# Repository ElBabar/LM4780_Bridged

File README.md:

# LM4780_Bridged

LM4780 (gainclone) amplifier board, bridged design (mono).

Bridged design of the LM4780, provides 120W, one channel.

Supply +40, -40, GND

You might need to use my library:
add https://github.com/ElBabar/Libabar.git
to your KiCad paths.

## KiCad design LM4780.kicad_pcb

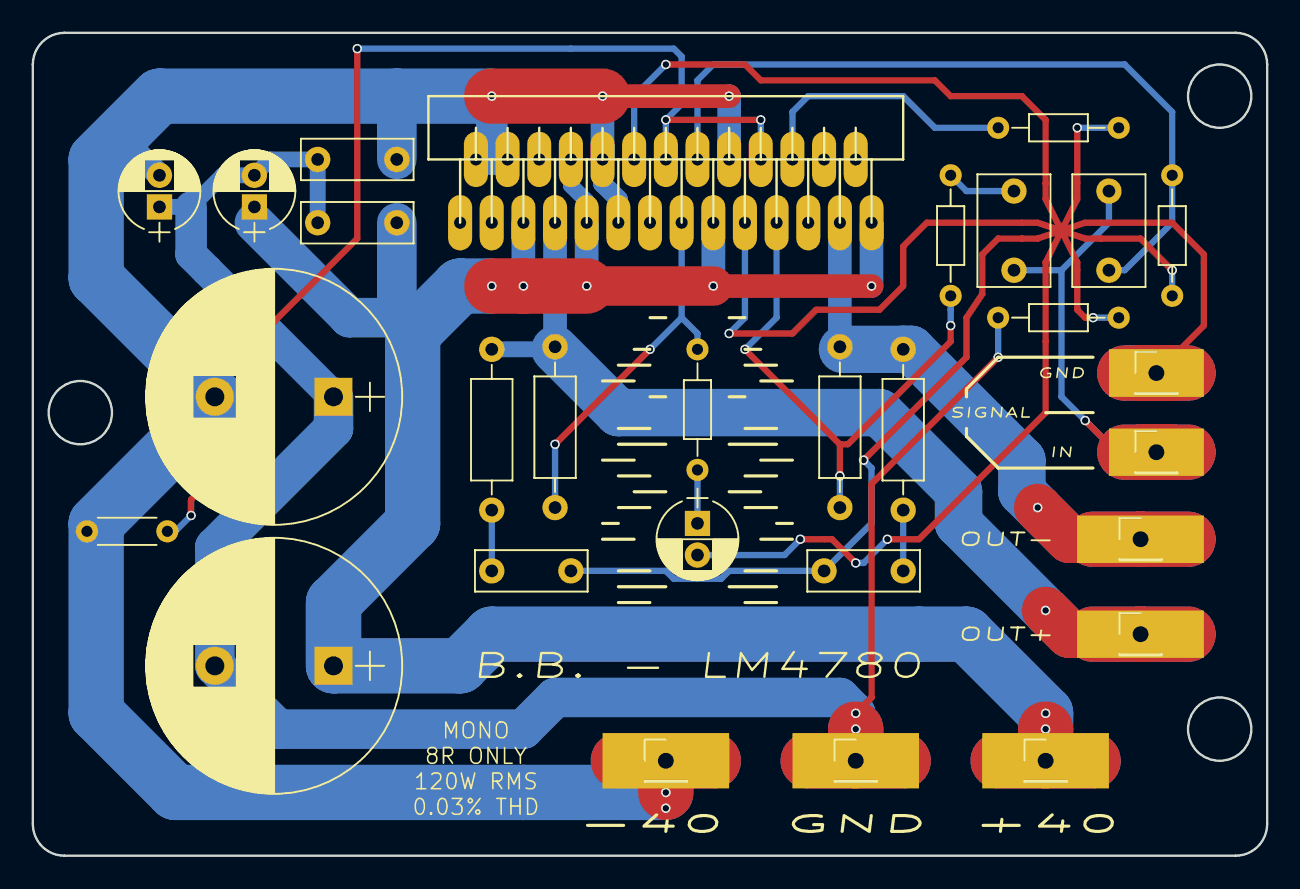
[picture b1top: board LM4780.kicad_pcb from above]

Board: 2 copper layers, 78.0 x 52.0 mm, 29 parts (0 on the bottom side), 16 nets.

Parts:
Ci1: 4.7µF; CP_Radial_D5.0mm_P2.00mm
Ci2: 4.7µF; C_Rect_L7.0mm_W4.5mm_P5.00mm
Cin1: 1µF; C_Rect_L7.0mm_W4.5mm_P5.00mm
Cs1, Cs2: 0.1µF; C_Rect_L7.0mm_W2.5mm_P5.00mm
Cs3, Cs4: 10µF; CP_Radial_D5.0mm_P2.00mm
Cs5, Cs6: 1000µF; CP_Radial_D16.0mm_P7.50mm
Csn1, Csn2: 0.1µF; C_Rect_L7.0mm_W2.5mm_P5.00mm
GND: CONN_01X01; Pin_Header_Straight_1x01_Pitch2.54mm
GND#2: CONN_01X01; Pin_Header_Straight_1x01_Pitch2.54mm
IN: CONN_01X01; Pin_Header_Straight_1x01_Pitch2.54mm
OUT+: CONN_01X01; Pin_Header_Straight_1x01_Pitch2.54mm
OUT-: CONN_01X01; Pin_Header_Straight_1x01_Pitch2.54mm
Rb2: 3.3K; R_Axial_DIN0204_L3.6mm_D1.6mm_P7.62mm_Horizontal
Rf1: 46.4K; R_Axial_DIN0207_L6.3mm_D2.5mm_P10.16mm_Horizontal
Rf2: 51.1K; R_Axial_DIN0207_L6.3mm_D2.5mm_P10.16mm_Horizontal
Rg1: 2.7R; R_Axial_DIN0204_L3.6mm_D1.6mm_P7.62mm_Horizontal
Ri1, Ri2: 4.7K; R_Axial_DIN0204_L3.6mm_D1.6mm_P7.62mm_Horizontal
Rin1: 47K; R_Axial_DIN0204_L3.6mm_D1.6mm_P7.62mm_Horizontal
Rm1: 10K; R_Axial_DIN0204_L3.6mm_D1.6mm_P5.08mm_Horizontal
Rsn1, Rsn2: 2.7R; R_Axial_DIN0207_L6.3mm_D2.5mm_P10.16mm_Horizontal
U1: LM4780
V+: CONN_01X01; Pin_Header_Straight_1x01_Pitch2.54mm
V-: CONN_01X01; Pin_Header_Straight_1x01_Pitch2.54mm

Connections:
/+IN_A: Cin1.2, Rin1.1, U1.16
/+IN_B: Rb2.1, U1.22
/-IN_A: Rf1.1, Ri1.1, U1.15
/-IN_B: Rf2.1, Ri2.2, U1.21
/AUDIO: Ci2.1, Cin1.1, IN.1
/MUTE: Rm1.1, U1.14, U1.20
/OUT_A: OUT+.1, Rf1.2, Rsn1.1, U1.7
/OUT_B: OUT-.1, Rf2.2, Rsn2.1, U1.25
/V+: Cs1.1, Cs3.1, Cs5.1, U1.5, U1.8, U1.9, U1.17, U1.27, V+.1
/V-: Cs2.1, Cs4.2, Cs6.2, Rm1.2, U1.2, U1.4, U1.10, U1.11, U1.18, V-.1
GND: Cs1.2, Cs2.2, Cs3.2, Cs4.1, Cs5.2, Cs6.1, GND.1, Rg1.1
GNDA: Ci1.2, Csn1.2, Csn2.2, GND#2.1, Rb2.2, Rg1.2, Rin1.2, U1.12, U1.19
unnamed: Ci1.1, Ri1.2
unnamed: Ci2.2, Ri2.1
unnamed: Csn1.1, Rsn1.2
unnamed: Csn2.1, Rsn2.2
